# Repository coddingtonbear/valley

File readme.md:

# Whiterose: A DIY Rescuetime + ESP32 Productivity Monitor IOT Device

Whiterose is a DIY project you can use for building a (relatively) simple device for giving you an up-to-date assessment of how productive (or distracted) you are.

## Parts List (BOM)

* 1x ESP32 ([~$4 on AliExpress](https://www.aliexpress.com/item/ESP-WROOM-32-ESP32-Bluetooth-and-WIFI-Dual-Core-CPU-with-Low-Power-Consumption-MCU/32793415575.html?spm=2114.search0104.3.26.5RzsyN&ws_ab_test=searchweb0_0,searchweb201602_4_10152_10065_10151_10130_10068_10344_10345_10547_10342_10546_10343_10340_10341_10548_10545_10541_10307_10060_10155_10154_10056_10055_10539_10537_10536_10059_10534_10533_100031_10103_10102_5670015_10142_10107_10324_5660015_10325_10562_10084_10083_10561_10178_10312_10313_10314_5650015_10550_10073_10551_10552_10553_10554_10557_10558-10552,searchweb201603_2,ppcSwitch_5&btsid=a117c8df-c8ed-4f43-8924-000555686ad1&algo_expid=a394fe7b-2047-489e-8816-9dba91acb8ad-3&algo_pvid=a394fe7b-2047-489e-8816-9dba91acb8ad))
* 1x CH341A USB->UART ([~$1 on AliExpress](https://www.aliexpress.com/item/Free-shipping-CH341A-SOP28-USB-bus-switching-chip/32465435558.html?spm=2114.search0104.3.296.82WrhQ&ws_ab_test=searchweb0_0,searchweb201602_4_10152_10065_10151_10130_10068_10344_10345_10547_10342_10546_10343_10340_10341_10548_10545_10541_10307_10060_10155_10154_10056_10055_10539_10537_10536_10059_10534_10533_100031_10103_10102_5670015_10142_10107_10324_5660015_10325_10562_10084_10083_10561_10178_10312_10313_10314_5650015_10550_10073_10551_10552_10553_10554_10557_10558-10552,searchweb201603_2,ppcSwitch_5&btsid=278ad066-3504-4684-8782-9417db61a984&algo_expid=eaf47891-7115-42b5-9a58-e7a70337a5e1-37&algo_pvid=eaf47891-7115-42b5-9a58-e7a70337a5e1))
* 1x 1.8inch TFT LCD Module using ST7735R ([~5 on AliExpress](https://www.aliexpress.com/item/1-8-inch-TFT-LCD-Display-Module-with-PCB-Board-ST7735R-Drive-IC-SPI-Serial-Interface/32350099643.html?spm=a2g0s.9042311.0.0.NYjAvA))
* 1x SLV6A RGB LED
* 1x UJ2-MIBH-4 USB Connector
* 1x AP1117-3.3v Voltage Regulator
* 1x HC49 12MHz SMD Crystal
* Miscellaneous passives
    * 2x 10Ω 0805 SMD Resistor (for blue/green LEDs)
    * 1x 150Ω 0805 SMD Resistor (for red LED)
    * 2x 10kΩ 0805 SMD Resistor (pull-ups)
    * 2x 22pF 0805 SMD Capacitor (for crystal -- may need adjustment depending upon your technique, see errata!)
    * 1x 0.1uF 0805 SMD Capacitor (for decoupling the CH341A)
    * 1x 220mF F-Size SMD Capacitor

## 3d Printing (STL Files)

See the `3d` folder of the project.

## Actual Photos

## Schematic

## Errata

The following are problems I encountered while making this board.  All have been corrected on the included schematics, but you may see my workarounds for these problems in the board photos above:

* If you look closely at photos of the board, you might notice that there was originally an SOT-23 package between the 3V3 line, a pin of the microcontroller, and the LCD panel's backlight control pin.  That device was a BSS138 transistor.  I had originally intended the LCD backlight to be controllable by the microcontroller, but hadn't considered the voltage drop across the transistor, and that voltage drop was sufficient enough when powered by a 3.3V power source for the backlight to no longer be able to turn on (if you look carefully at the photo, you might notice a tiny copper wire bridging two pins of the transistor).  In an earlier version of this board, I had used a different microcontroller that used a 5V power source instead of a 3.3V power source, so the voltage drop was accidentally not enough to prevent the backlight from lighting.  Not a huge deal, though, luckily.
* You may also notice that I don't have any capacitors between my crystal and ground.  This was definitely not something I was expecting, but it does seem like milled boards have higher intrinsic capacitance than boards that are etched otherwise.  You may actually need to populate SMD capacitors there -- I have in all other boards that I didn't mill.  22pF is a commonly-recommended value.
* You might notice a weird unsoldered via on the RTS line.  That was an accident!  I think I double-pressed `v` when routing that trace in KiCad and somehow didn't notice.

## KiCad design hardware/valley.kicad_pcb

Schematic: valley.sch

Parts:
C1, C2: 22p; 0805_Milling
C3: 0.1u; 0805_Milling
C12: 1000u; CAP-SMD-SIZE-F
D1: LED_RGB; SLV6A-FKB-MILLING
P2: USB_OTG; UJ2-MIBH-4-SMT
P4: CONN_01X16; Pin_Header_Straight_1x16_Pitch2.54mm
R1, R4: 10; 0805_Milling
R3, R7: 10k; 0805_Milling
R5: 150; 0805_Milling
U1: CH341A; SOIC-28W_7.5x17.9mm_Pitch1.27mm
U2: AP111733; SOT-223
U3: ESP32-WROOM
Y1: 12M; Crystal_SMD_HC49-SD_HandSoldering

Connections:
+3V3: C3.1, C12.1, P4.2, P4.15, R3.2, R7.1, U1.9, U1.28, U2.2, U2.4, U3.2
+5V: P2.1 (VBUS), U2.3
A0: P4.10, U3.11
CS_SD: P4.3, U3.26
CS_TFT: P4.7, U3.9
DTR: R7.2, U1.20, U3.25
GND: C1.1, C2.1, C3.2, C12.2, D1.1, D1.2, D1.3, P2.5 (GND), P2.6 (shield), P4.1, P4.16, U1.12, U1.27, U2.1, U3.1, U3.15, U3.38, U3.39
LED_BLUE: R1.2, U3.31
LED_GREEN: R4.2, U3.30
LED_RED: R5.2, U3.29
MISO: P4.5, U3.14
MOSI: P4.4, P4.9, U3.16
unnamed: C1.2, U1.13, Y1.1
unnamed: C2.2, U1.14, Y1.2
unnamed: D1.4, R1.1
unnamed: D1.5, R4.1
unnamed: D1.6, R5.1
RESET_TFT: P4.11, U3.10
RTS: R3.1, U1.21, U3.3
RXD: U1.5, U3.34
SCK: P4.6, P4.8, U3.13
TXD: U1.6, U3.35
UD+: P2.3 (D+), U1.10
UD-: P2.2 (D-), U1.11
USB_CONNECTED: U1.1, U3.33

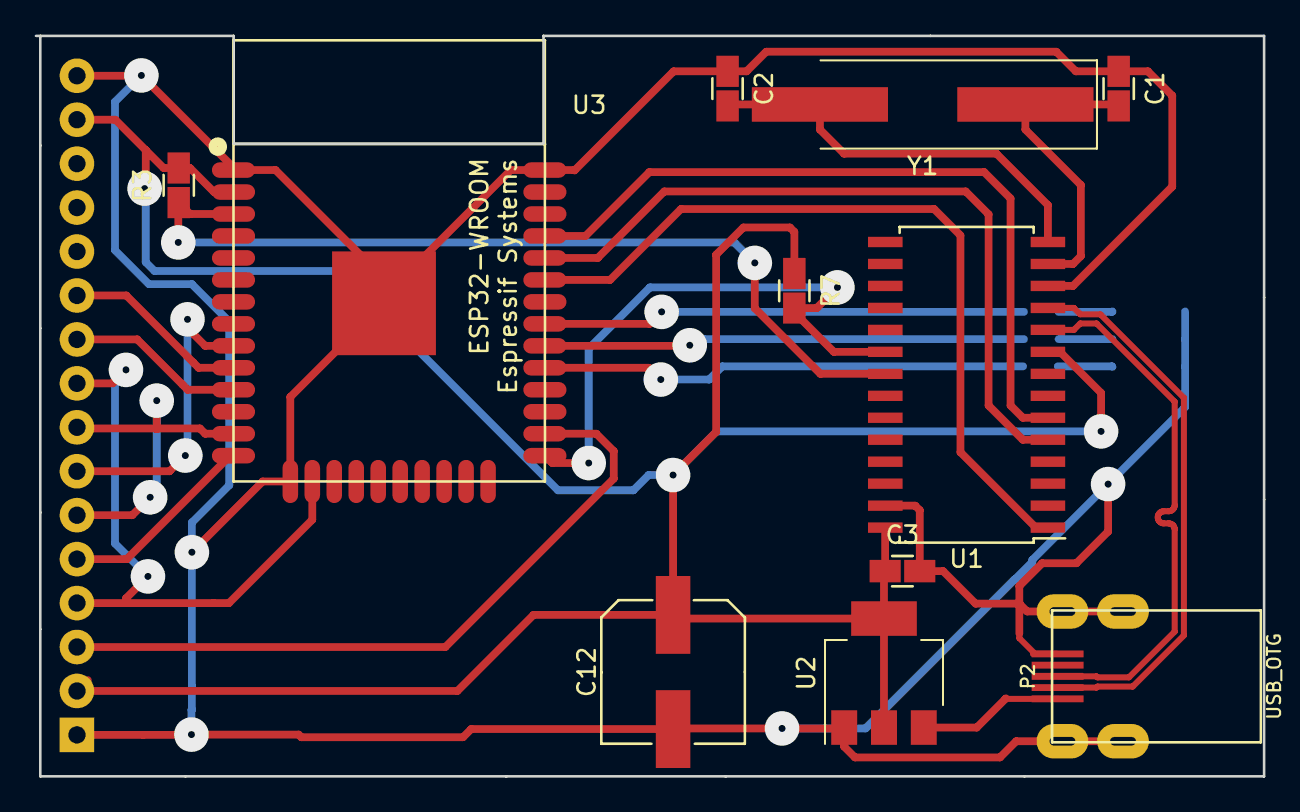
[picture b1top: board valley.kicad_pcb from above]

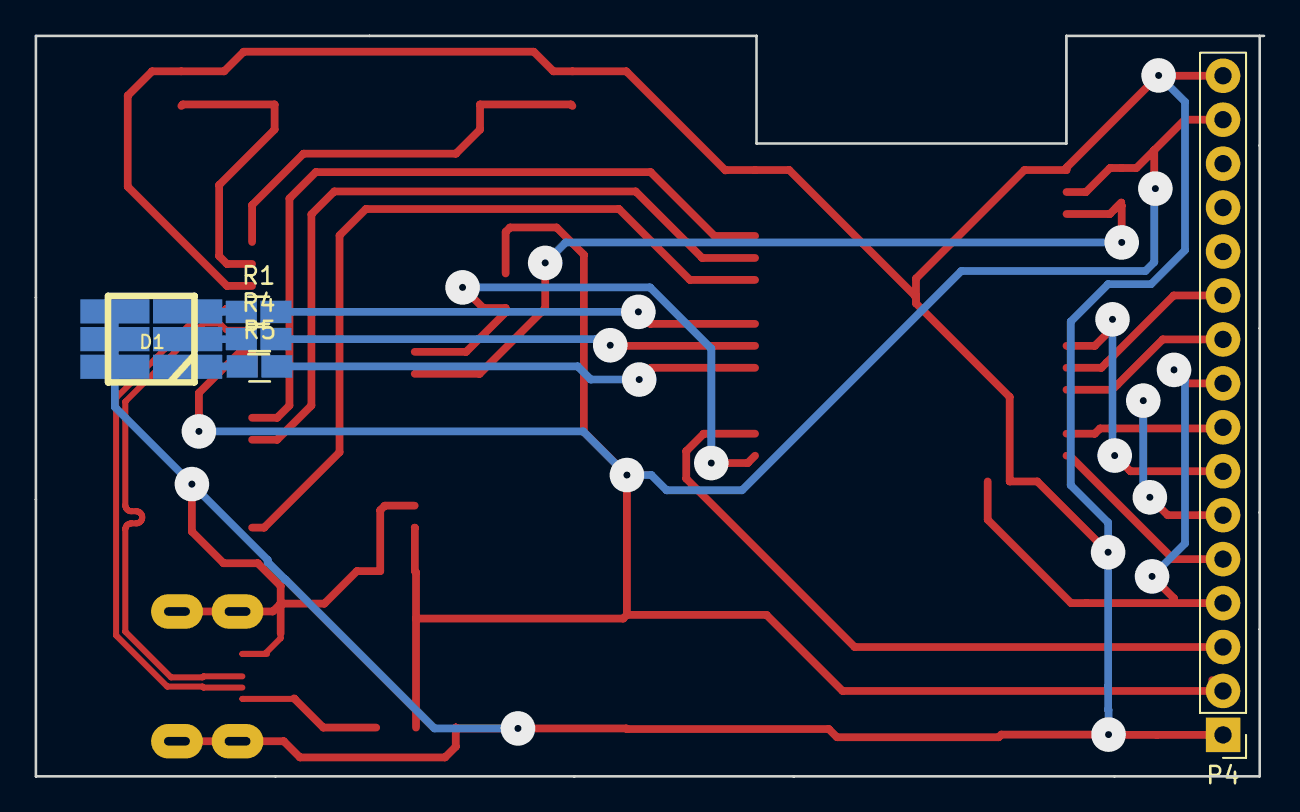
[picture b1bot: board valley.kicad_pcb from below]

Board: 2 copper layers, 71.0 x 42.8 mm, 16 parts (5 on the bottom side), 25 nets.

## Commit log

2017-04-10 And so it begins...
2017-04-10 Moving LED to back of board.
2017-04-11 Updating schematic to link SDA/MOSI and SCL/SCK.
2017-04-15 Removing some unnecessary pullup resistors.
2017-04-17 Updating schematics for wider trace width; 15mil is enough.
2017-04-24 Updating schematic for v 1.1.
2017-06-19 Adding final enclosure design.
2017-06-19 Adding latest schematic.
2017-06-19 Refactoring display into its own class.
2017-06-25 Fully-working, now.
2017-06-25 Fewer bugs...
2017-06-25 Better fonts.
2017-06-25 Apparently Color565 expects a BGR value instead of RGB.
2017-06-27 Calculate value using most recent 60m of time.
2017-06-29 Switching to a Eurostile-y font.
2017-06-30 Adding LED throbbing support; adding Michroma font.
2017-07-17 Updating color display for values <50.
2017-10-07 Updating to latest kicad version before next iteration.
2017-10-08 ESP12E version laid out.
2017-10-08 Removing top copper nonsignal layer.
2017-10-09 I just realized that I don't need a ground plane -- with milling, I get a copper layer for free.
2017-10-27 Updating to use ESP32 as main processor -- no need of the separate LED driver or I2C IO expander.
2017-10-28 Swapping CH340G to CH341A
2017-10-28 Setting reference point.
2017-10-29 Swapping ATMEGA1284 for an ESP32 -- no driver necessary now.
2017-10-29 Adding configuration variables for wifi ssid/pwd.
2017-10-30 Pulse the LED to indicate direction of productivity change.
2017-10-30 Make the LED slightly less bright.
2017-10-30 If there are no rows; return zero.
2017-11-03 Calculate max color values by using LEDC_TIMER_BIT rather than having hard-coded values.
2017-11-03 Process display loop prior to beginning main runloop.
2017-11-03 Distinguish between HTTP errors and connection errors; do not emit error message for the latter.
2017-11-03 Slightly tweak colors used for displaying productivity changes.
2017-11-04 Minor changes to LED colors.
2017-11-07 Minor changes for updating to VSCode's platformio integrated ide.
2017-11-07 Updating to allow multiple WiFi AP passwords.
2017-11-07 Run LED breathing l oop on the other core.
2017-11-07 Minor changes to LED colors and effects.
2017-11-07 Minor schematic updates.
2017-11-07 Ignore future changes to configuration.h.
2017-11-07 Updating readme; adding 3d files, etc.
2017-11-07 Updating displayed gif.
2017-11-07 Updating to use youtube-provided image.
